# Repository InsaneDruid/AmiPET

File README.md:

# AmiPET
A simple Arduino Shield which offers the possibility to use Amiga keyboards on Commodore PET computers.
It uses the Arduino to communicate with an Amiga keyboard and control a M3493B2 Crosspoint to switch the PET keyboard matrix.

[Schematic](https://github.com/InsaneDruid/AmiPET/blob/main/AmiPET.pdf "Schematic")  

[Bill of Materials](https://htmlpreview.github.io/?https://github.com/InsaneDruid/AmiPET/blob/main/bom/AmiPET_bom.html "Bill of Materials")

## Background
Amiga side sends *rawkey* codes to the Arduino. An array of tupels contains bitvalues for the M3493B2 to switch the PET keyboard matrix rows and columns to the appropriate key. Entries represent Amiga rawkey codes #00 to #68 (0-103 decimal).

The sketch uses Arduino port bitwise operations to keep the latency low. Row values are encoded by bitvalues of 1 2 4 6 on bits 0-3 (logic hole in M3493B2), bits 4-6 are unused , bit 7 marks undefined keys (no PET key will be sent).
Colum bits are leftshifted 2 bits to accomodate Arduino port setup (PD0, PD1 left free for serial communication) and encode bitvalues of 1 2 4 on bits 2-4. Bit 0,1,5,6 are unused, Bit7 of marks shifted keys (cursor left/up). On those the arduino will send a Shift key press/release before sending the encoded key to the PET.

## How to change the Key Bindings
+ Get desired PET matrix entry and Amiga rawkey code.
+ Edit the (n+1)th tupel of *key_matrix* in *Amiga_PETkey.h* where n = amiga rawkey code.
+ Encode PET Row Number with bitvalues of 1 2 4 6 for bits 0-3. Set bit 7 if no PET key should be generated for this amiga key.
+ Encode PET Column Number with bitvalues 1 2 4 for bits 2-4. Set bit 7 if key should be shifted on PET side.

### Example1
Amiga *6* to PET *6*

+ Rawkey code of Amiga *6* key is #06 = 6 decimal, so edit the 7th tupel in the key_matrix array.
+ The keyboard scan matrix for the *6* key on a UK PET Business keyboard is *Row 9 Colum 2*
+ As the M2493B2 interprets the 4th row bit as 6 instead of 8, the row entry is 0b00001011.
+ Column entry is 2bit leftshifted binary representation of decimal 2.

Result: {0b00001011, 0b00001000}

### Example2
Amiga *Cursor Up* to PET *Shift+Cursor Up/Down*

+ Rawkey code of *Amiga Cursor Up* key () is #4C = 76 decimal, so edit the 77th tupel in the key_matrix array.
+ The keyboard scan matrix for the *Cursor Up/Down* key on a UK PET Business keyboard is *Row 5 Colum 4*.
+ The Row entry is a straigt binary representation of decimal 5.
+ Column entry is 2bit leftshifted binary representation of decimal 4 with bit 7 set addintionally to press/release shift before the *Cursor Up/Down* key on the PET side.

Result: {0b00000101, 0b10010000}

## Connecting the Adapter
+ The PET can supply unregulated 9VDC via the internal *RAWPwr" Headers (J11 on a universal Board) to both the Arduinos *VIN* pin and the M3493B2.
+ The Amiga keyboard needs +5V and GND from the Arduino as well as a connection to KBCLK (Arduino PC4) and KBData (Arduino PC5)
+ The PET keyboard connector gets connected to the X0-X9 pins (rows) and the Y0-Y7 pins (colums) of the M3493B2 as well as Ground.

## Printable Parts

+ *DIN_Connector_Mount .stl* can be used to mount the DIN Connector in place of the keyboard connector of an 8032-SK/8296.
+ *Case_Top.stl* and *Case_Bottom.stl* are designed to fit an Uno with the M3493B2 shield mounted.

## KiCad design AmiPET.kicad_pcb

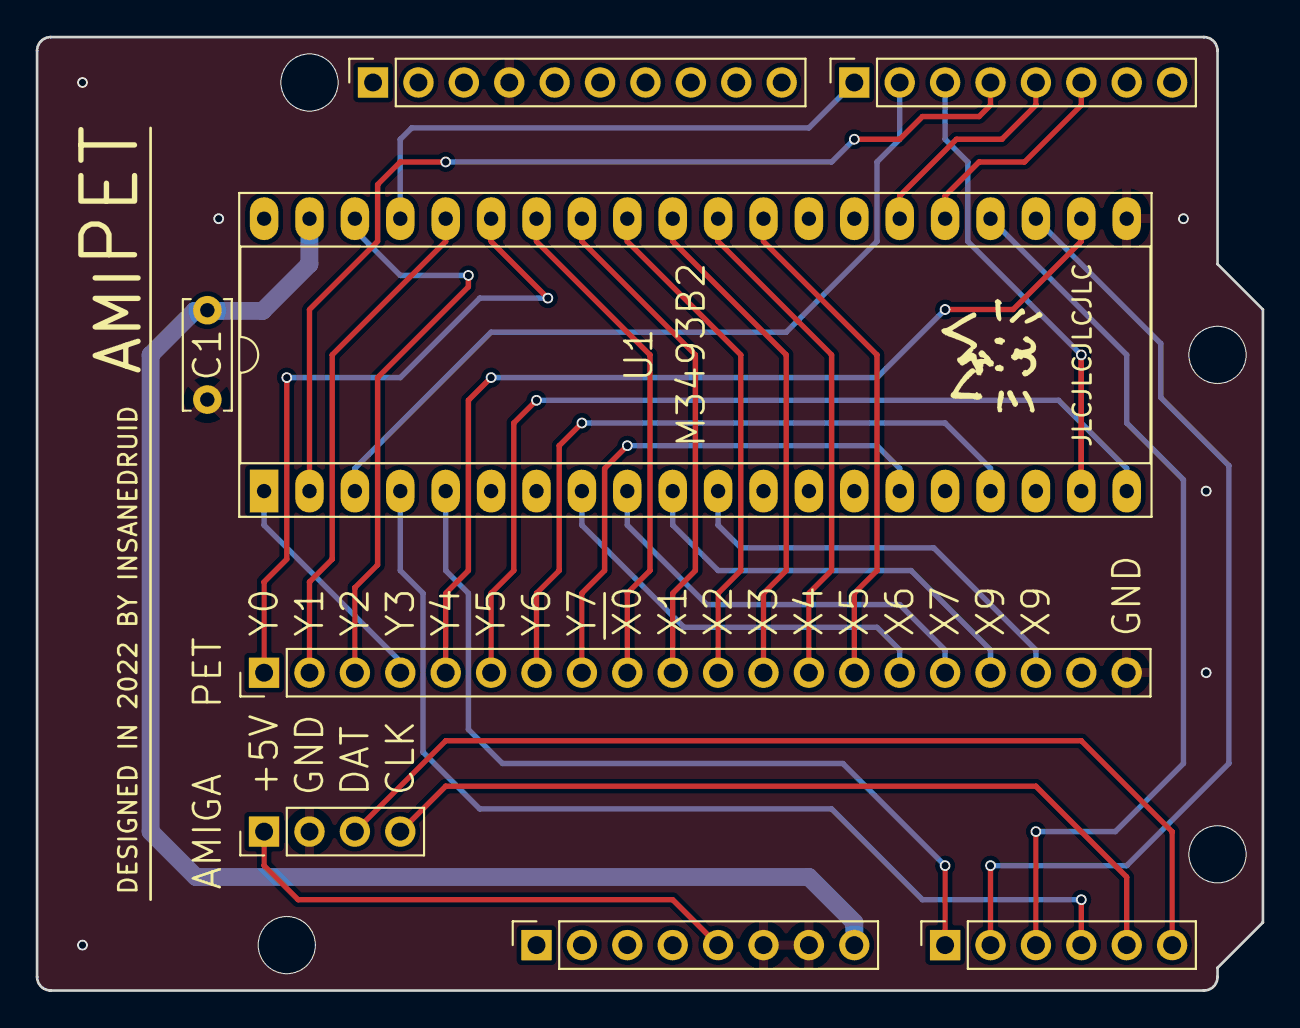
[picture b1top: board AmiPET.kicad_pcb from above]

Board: 2 copper layers, 68.6 x 53.3 mm, 12 parts (0 on the bottom side), 33 nets.

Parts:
C1: C; C_Disc_D6.0mm_W2.5mm_P5.00mm
J1: Power; PinSocket_1x08_P2.54mm_Vertical
J2: Digital/PWM; PinSocket_1x10_P2.54mm_Vertical
J3: Analog; PinSocket_1x06_P2.54mm_Vertical
J4: Digital/PWM; PinSocket_1x08_P2.54mm_Vertical
J6: PET Keyboard Connector; PinHeader_1x20_P2.54mm_Vertical
J7: AMIGA Keyboard Connector; PinHeader_1x04_P2.54mm_Vertical
MH1, MH2, MH3, MH4: MountingHole_3.2mm
U1: M3493B2; DIP-40_W15.24mm_Socket_LongPads

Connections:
+5V: J1.5, J7.1
/AX0: J3.1, U1.5 (AX0)
/AX1: J3.2, U1.23 (AX1)
/AX2: J3.3, U1.24 (AX2)
/AX3: J3.4, U1.4 (AX3)
/AY0: J4.6, U1.25 (AY0)
/AY1: J4.5, U1.26 (AY1)
/AY2: J4.4, U1.2 (AY2)
/DATA: J4.1, U1.37 (DATA)
/KCLK: J3.5, J7.4
/KDAT: J3.6, J7.3
/RESET: J4.2, U1.3 (RESET)
/STROBE: J4.3, U1.19 (STROBE)
/X0: J6.9, U1.34 (X0)
/X1: J6.10, U1.33 (X1)
/X2: J6.11, U1.32 (X2)
/X3: J6.12, U1.31 (X3)
/X4: J6.13, U1.30 (X4)
/X5: J6.14, U1.29 (X5)
/X6: J6.15, U1.8 (X6)
/X7: J6.16, U1.9 (X7)
/X8: J6.17, U1.10 (X8)
/X9: J6.18, U1.11 (X9)
/Y0: J6.1, U1.35 (Y0)
/Y1: J6.2, U1.36 (Y1)
/Y2: J6.3, U1.38 (Y2)
/Y3: J6.4, U1.1 (Y3)
/Y4: J6.5, U1.22 (Y4)
/Y5: J6.6, U1.20 (Y5)
/Y6: J6.7, U1.17 (Y6)
/Y7: J6.8, U1.15 (Y7)
GND: C1.2, J1.6, J1.7, J2.4, J6.20, J7.2, U1.21 (VSS)
VCC: C1.1, J1.8, U1.39 (VDD)

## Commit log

2021-01-14 Updated Content
2022-12-09 PCB Project added
2022-12-09 Cleanup & Added gitignore
2023-06-18 PCB Project update
    tweaked layout
    new 3d models
    added schematic, production files, bom and image
    removed old painted schematic
2023-06-18 case render
2024-02-16 added jlc order number markers
    added jlc order number position marker to pcb
    fixed licence links in drawing sheets to match board prints, readme and project
    added desktop ini to gitignore

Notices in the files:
AmiPET.kicad_pcb:
creativecommons.org/licenses/by-sa/4.0
creativecommons.org/licenses/by/4.0
License: CC BY-SA 4.0
